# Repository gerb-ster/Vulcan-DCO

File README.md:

# Vulcan DCO

## Status: (Almost) finished*

- done: draw first schematic
- done: breadboard and test
- done: board design
- done: design frontpanel
- done: order PCB and build prototype

*) I only need to finish building a proper faceplate; otherwise this project is done.

## Theory

This DCO module is based on an article written by Alethea Flowers about the Roland Juno series. 
The idea behind this specific DCO is that a (analog) ramp generator is being controlled by 
a (digital) microcontroller. A clock signal comming from the micro controller will control the 
frequency of the ramp generator. The nature of this perticular circuit is such, that an increase of 
the frequency means an decrease of the output amplitude of the generated waveform. To counter 
this effect, a DAC is used to compensate the input voltage. If you want more in-depth information
about this, I would highly recommend you read the above mentioned article. A link is provided below.

## Requirements

For this module I aimed at the following specs

- 1v/oct control voltage (-3v to +5v)
- 8 octave range (A0 to A8)
- Triangle, Saw, Sine, Pulse, Square and Sub-Square outputs
- 1k output impedance
- 10 Vpp around 0 volts output
- PWM control for the Pulse output

## Internals

Since this systems requires a micro controller to control it, I've choosen the ATTiny84 running at 20Mhz
from Microchip for this purpose. It has all peripherals (ADC, timers, SPI) on board and it has a relative
small footprint. For the DAC I've choosen a MCP4921 which is connected to the ATTiny through SPI. To generate
a stabel reference voltage, a TL431 shunt voltage regulator is used. For all other tasks, scaling and shifting
the CV and wave generators, TL082/TL084 op-amps are used.

## General Workings

The control voltage comming in is scaled down by 2 and shifted down to 0v to translate the -3v/+5v into 0v/+4v.
Diode clamps are used to make sure the signal doesn't go below 0v or +5v. This signal is then fed to the 10bit 
ADC of the microchip, which has a AREF of 4v, so 0v has a value of 0, while 4v will have a value of 1024. This 
value is then used to determine the input voltage of the ramp genator using the DAC and the clock signal which 
controls it's frequency. The generated ramp wave is then used to generate the sine, triangle, and pulse waves
using several wave shapers. The square and sub square waves are taken directly from the clock signal comming 
from the microchip.

A simple block diagram outlining the inner workings

## The Microchip

The most interresting part of this system is the microchip controlling the ramp generator. All other parts are
more or less standard building blocks which you will find in various other VCO schematics. As mentioned above,
the microchip uses it's ADC to convert the incoming control voltage to a 10bit value which is used to control
the ramp generator. To do this, every one of these 1024 values needs to be translated to a certain clock 
frequency and an input voltage. Since this is not a linear scale, some math has to be done. I've tried to break
it down in the following sections:

### CV to Frequencies

I've used this table to translate the control voltages to frequencies. I've also added the CV value after shifting
and scaling and the correspondending ADC values. 

| CV | Norm. CV | Note | Hz | ADC Value  |
|---|---|---|---|---|
| -3v | 0.0v | A0 | 27.5 Hz | 0
| -2v | 0.5v | A1 |   55 Hz | 127
| -1v | 1.0v | A2 |  110 Hz | 255
| 0v | 1.5v | A3 |  220 Hz | 383
| 1v | 2.0v | A4 |  440 Hz | 511
| 2v | 2.5v | A5 |  880 Hz | 639
| 3v | 3.0v | A6 | 1760 Hz | 767
| 4v | 3.5v | A7 | 3520 Hz | 895
| 5v | 4.0v | A8 | 7040 Hz | 1023

The formula used here is:

```
frequency = (2 ^ (2 * normalized_control_voltage)) * 27.5
```

### Setting the Clock Frequency

For the clock signal I've used one of the Timers (timer1) of the ATTiny84. It is set up in such a
way that it generates a square wave at pin 7 with a frequency set by manipulating a compare mode
value. If you want more specifics and want to know what registers are set, please check out the 
source code, comments are provided. For every duty cycle of the squeare wave we need 2 pulses, one
to turn the output high, one to turn it low. This formula is used ('F_CPU' is the clock speed of the
CPU (20Mhz) and 'current_prescaler' is the prescaler used in this timer(8)):

```
timer_value = (F_CPU / current_prescaler) / (frequency * 2)
```

For more information about using the timer of an ATTiny84, links are provided below.

### Input Voltage Compensation

As mentioned above, we need to compensate the input voltage of the ramp generator to make sure the
amplitude of the output remains the same. To do this we use a DAC. The DAC generates a voltage between
0v and 4v, using a 12bit value (0-4096). For this we also use the 4.00v shunt voltage regulator as a
voltage reference. This voltage is then inverted and multiplied with a factor 3 to cover a range of
0v to -12v. This way the ramp generator will output a 12vpp ramp between 0v and 12v.

The formula to transform a frequency to the appropriate DAC voltage can be found in the article by
Alethea Flowers, she explains it in much better details then I can do, so if you're interested in that,
the link can be found below.

```
C = 1nF
R = 200k Ohm
Vout = +12v

time = 1 / frequency
Vin = -(C * R * Vout) / time
```

#### However... 

After a lot of testing and doing measurements I found out that this formula works, but it kind of 
starts failing for the lower frequencies. Below 300Hz you will need a higher input voltage to get a consistent
output voltage. To make it easier for myself I've picked an 10Vpp instead of 12Vpp for my measurements. I've
plotted these numbers on a graph and it turned out pretty linear so when i used the formula which came out
this graph, the low end output voltage are much more consistent.

I'm not a mathematician so why or how this formula works, i don't know :-)

```
Vin = (0.697151065 * frequency) + 40.82
```

### Lookup Tables

If you look through the source code you won't find any of the above decribed formulas. This is because 
I've used 2 lookup tables to speed things up. Although the ATTiny84 could do the Math involved, this is 
not really necessary. Every one of the 1024 values coming from ADC will translate into a 'fixed' timer and 
DAC value. So there is no real need to calculate these values on the fly. These lookup tables are basically 
2 giant arrays, 1024 elements in size, which contain all pre-calculated values. These arrays are stored in
the Flash memory of the ATTiny since the normal RAM is to small. 

In the 'utils' folder you can find the ```generator.php``` file which is used to generate those tables and 
code. I've choosen to use PHP for this, because this is my 'native' language :-).

## Waveshapers

The Square and Sub-Square outputs are derived directly from the Clock signal using various op-amps and a 
CD4013 Dual Flip-Flop IC. This schematic is taken from a design for the 'making music with a 566' by
Thomas Henry. Next, the Saw Wave coming out of the Ramp generator is used to shape it into a Triangle wave.
This Triangle wave is then used to generate a Sine wave. The Saw wave is also used to create a Pulse wave.
There is a CV input and pot to control the Pulse Width Modulation. For these wave shapers I've used 
designs from Thomas Henry, Ray Wilson and Yves Usson (YUSynth). Links are found below.

## Calibration

There are 2 trimmerpots that need to be set, in order to calibrate the Ramp Generator Core. 

CV_OFFSET => -1.5v  
VREF_SET => 4.00v  

## Links

<https://blog.thea.codes/the-design-of-the-juno-dco/>  
<https://www.geogebra.org/graphing/mfdyqrfj>  
<https://www.bristolwatch.com/ccs/TL431A.htm>  
<https://github.com/JChristensen/tinySPI>  
<https://github.com/MetreIdeas/ATtinyx4A_ADC_Example>  
<https://eleccelerator.com/avr-timer-calculator/>  
<https://maxembedded.wordpress.com/2011/06/28/avr-timers-timer1/>  
<https://www.nongnu.org/avr-libc/user-manual/pgmspace.html>  
<https://www.arduino.cc/reference/tr/language/variables/utilities/progmem/>  
<https://www.birthofasynth.com/Thomas_Henry/Pages/VCO-1.html>  
<https://yusynth.net/Modular/EN/VCO/index.html>

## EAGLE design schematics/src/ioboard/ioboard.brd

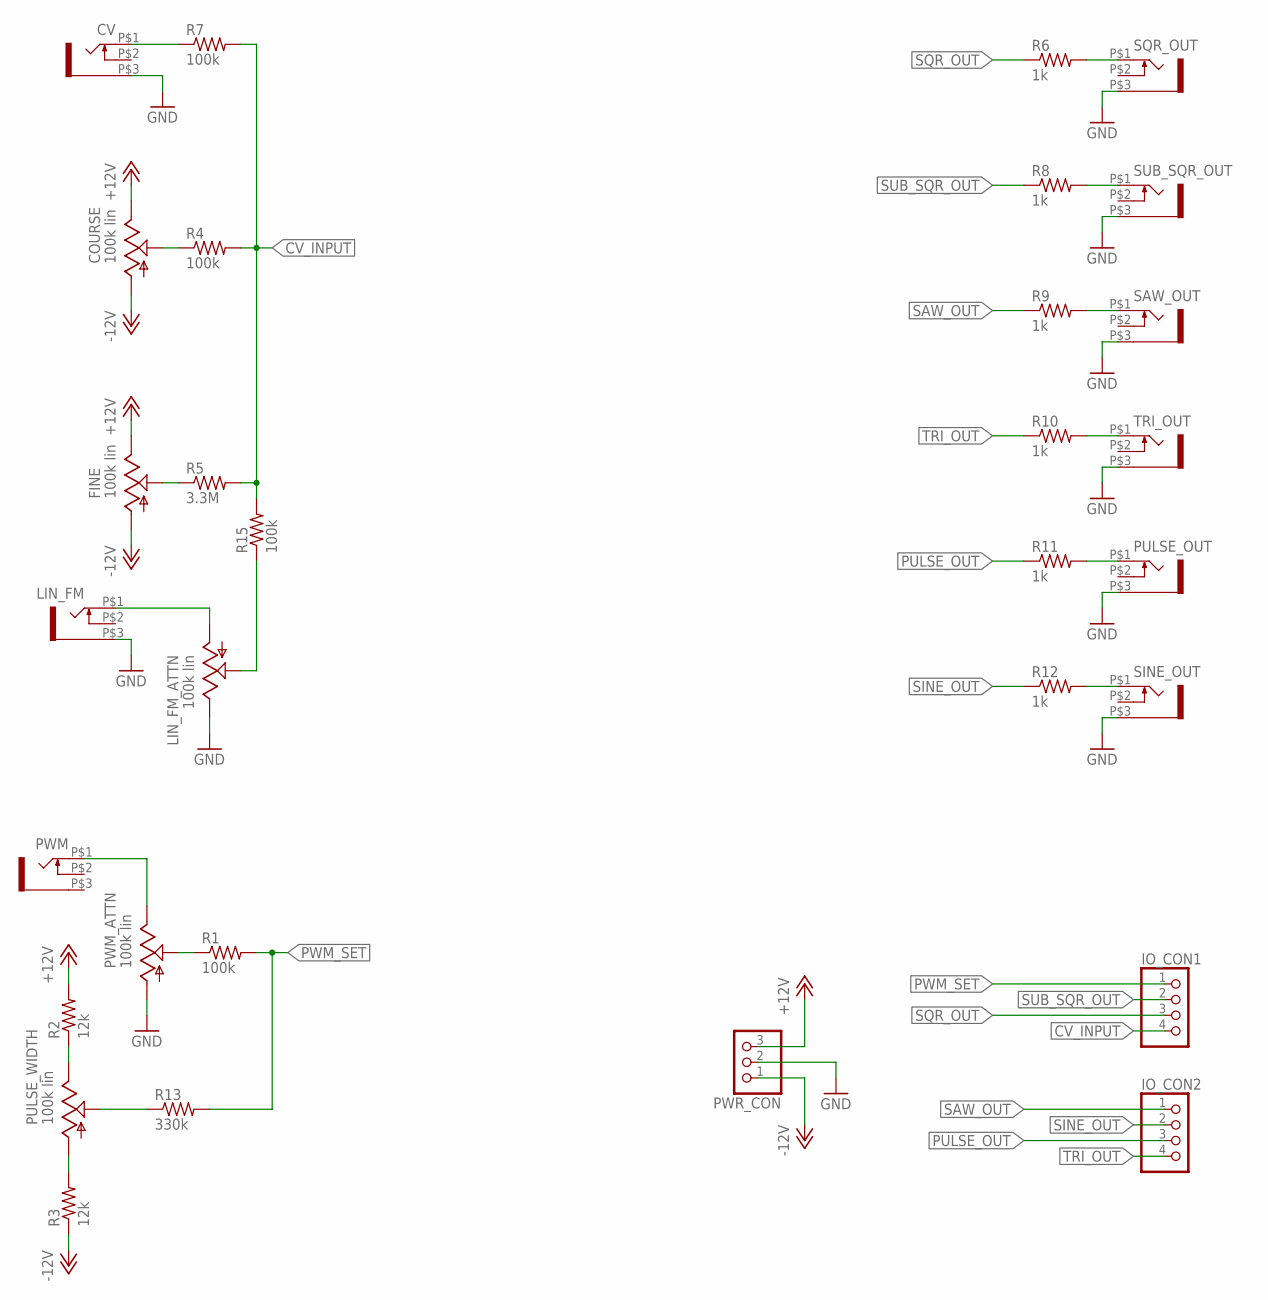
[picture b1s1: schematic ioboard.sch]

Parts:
COURSE: 100k lin; EVUF
CV: WQP-PJ301M-12_JACK
FINE: 100k lin; EVUF
IO_CON1, IO_CON2: PINHD-1X4; 1X04
LIN_FM: WQP-PJ301M-12_JACK
LIN_FM_ATTN: 100k lin; EVUF
PULSE_OUT: WQP-PJ301M-12_JACK
PULSE_WIDTH: 100k lin; EVUF
PWM: WQP-PJ301M-12_JACK
PWM_ATTN: 100k lin; EVUF
PWR_CON: PINHD-1X3; 1X03
R1, R4, R7, R15: 100k; 0207/7
R2, R3: 12k; 0207/7
R5: 3.3M; 0207/7
R6, R8, R9, R10, R11, R12: 1k; 0207/7
R13: 330k; 0207/7
SAW_OUT: WQP-PJ301M-12_JACK
SINE_OUT: WQP-PJ301M-12_JACK
SQR_OUT: WQP-PJ301M-12_JACK
SUB_SQR_OUT: WQP-PJ301M-12_JACK
TRI_OUT: WQP-PJ301M-12_JACK

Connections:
+12V: COURSE.3 (E), FINE.3 (E), PWR_CON.3, R2.2
-12V: COURSE.1 (A), FINE.1 (A), PWR_CON.1, R3.1
CV_INPUT: IO_CON1.4, R4.2, R5.2, R7.2, R15.2
GND: CV.P$3 (1), LIN_FM.P$3 (1), LIN_FM_ATTN.3 (E), PULSE_OUT.P$3 (1), PWM_ATTN.1 (A), PWR_CON.2, SAW_OUT.P$3 (1), SINE_OUT.P$3 (1), SQR_OUT.P$3 (1), SUB_SQR_OUT.P$3 (1), TRI_OUT.P$3 (1)
unnamed: COURSE.2 (S), R4.1
unnamed: FINE.2 (S), R5.1
unnamed: PULSE_WIDTH.3 (E), R2.1
unnamed: CV.P$1 (2), R7.1
unnamed: R6.2, SQR_OUT.P$1 (2)
unnamed: R8.2, SUB_SQR_OUT.P$1 (2)
unnamed: R9.2, SAW_OUT.P$1 (2)
unnamed: R10.2, TRI_OUT.P$1 (2)
unnamed: PULSE_WIDTH.1 (A), R3.2
unnamed: R12.2, SINE_OUT.P$1 (2)
unnamed: PULSE_WIDTH.2 (S), R13.1
unnamed: PWM.P$1 (2), PWM_ATTN.3 (E)
unnamed: PULSE_OUT.P$1 (2), R11.2
unnamed: PWM_ATTN.2 (S), R1.1
unnamed: LIN_FM.P$1 (2), LIN_FM_ATTN.1 (A)
unnamed: LIN_FM_ATTN.2 (S), R15.1
PULSE_OUT: IO_CON2.3, R11.1
PWM_SET: IO_CON1.1, R1.2, R13.2
SAW_OUT: IO_CON2.1, R9.1
SINE_OUT: IO_CON2.2, R12.1
SQR_OUT: IO_CON1.3, R6.1
SUB_SQR_OUT: IO_CON1.2, R8.1
TRI_OUT: IO_CON2.4, R10.1

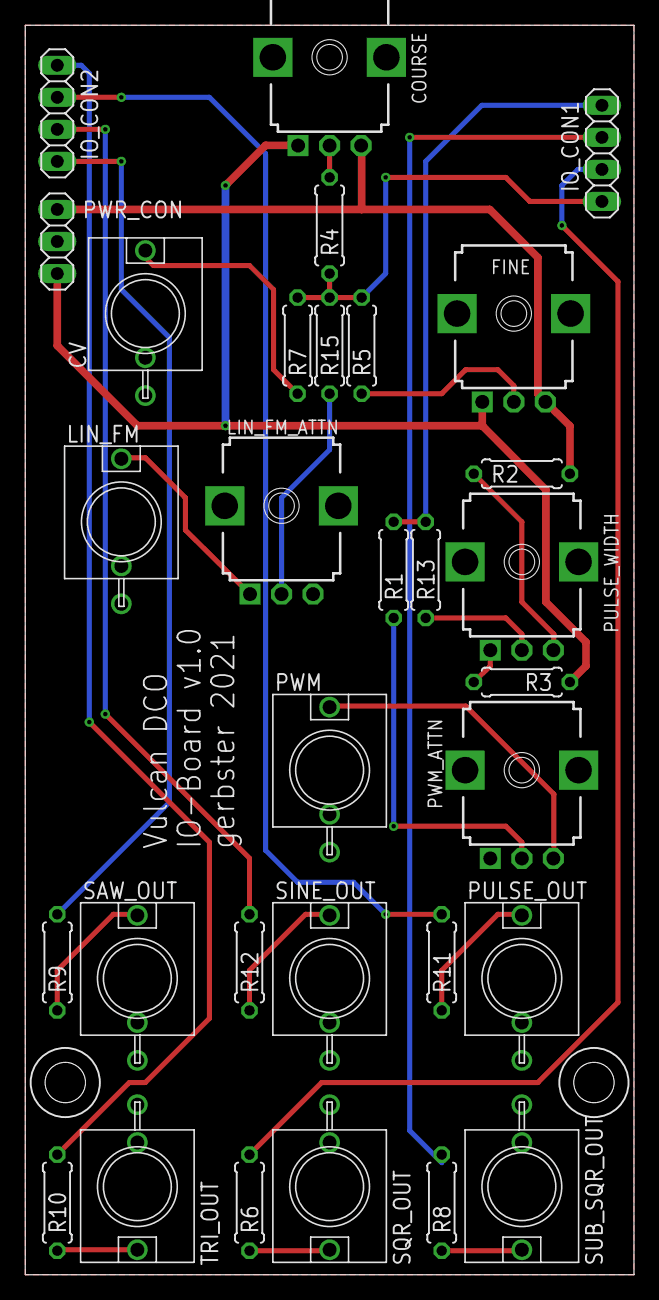
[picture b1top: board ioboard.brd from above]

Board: 2 copper layers, 48.3 x 99.1 mm, 31 parts (0 on the bottom side), 27 nets.

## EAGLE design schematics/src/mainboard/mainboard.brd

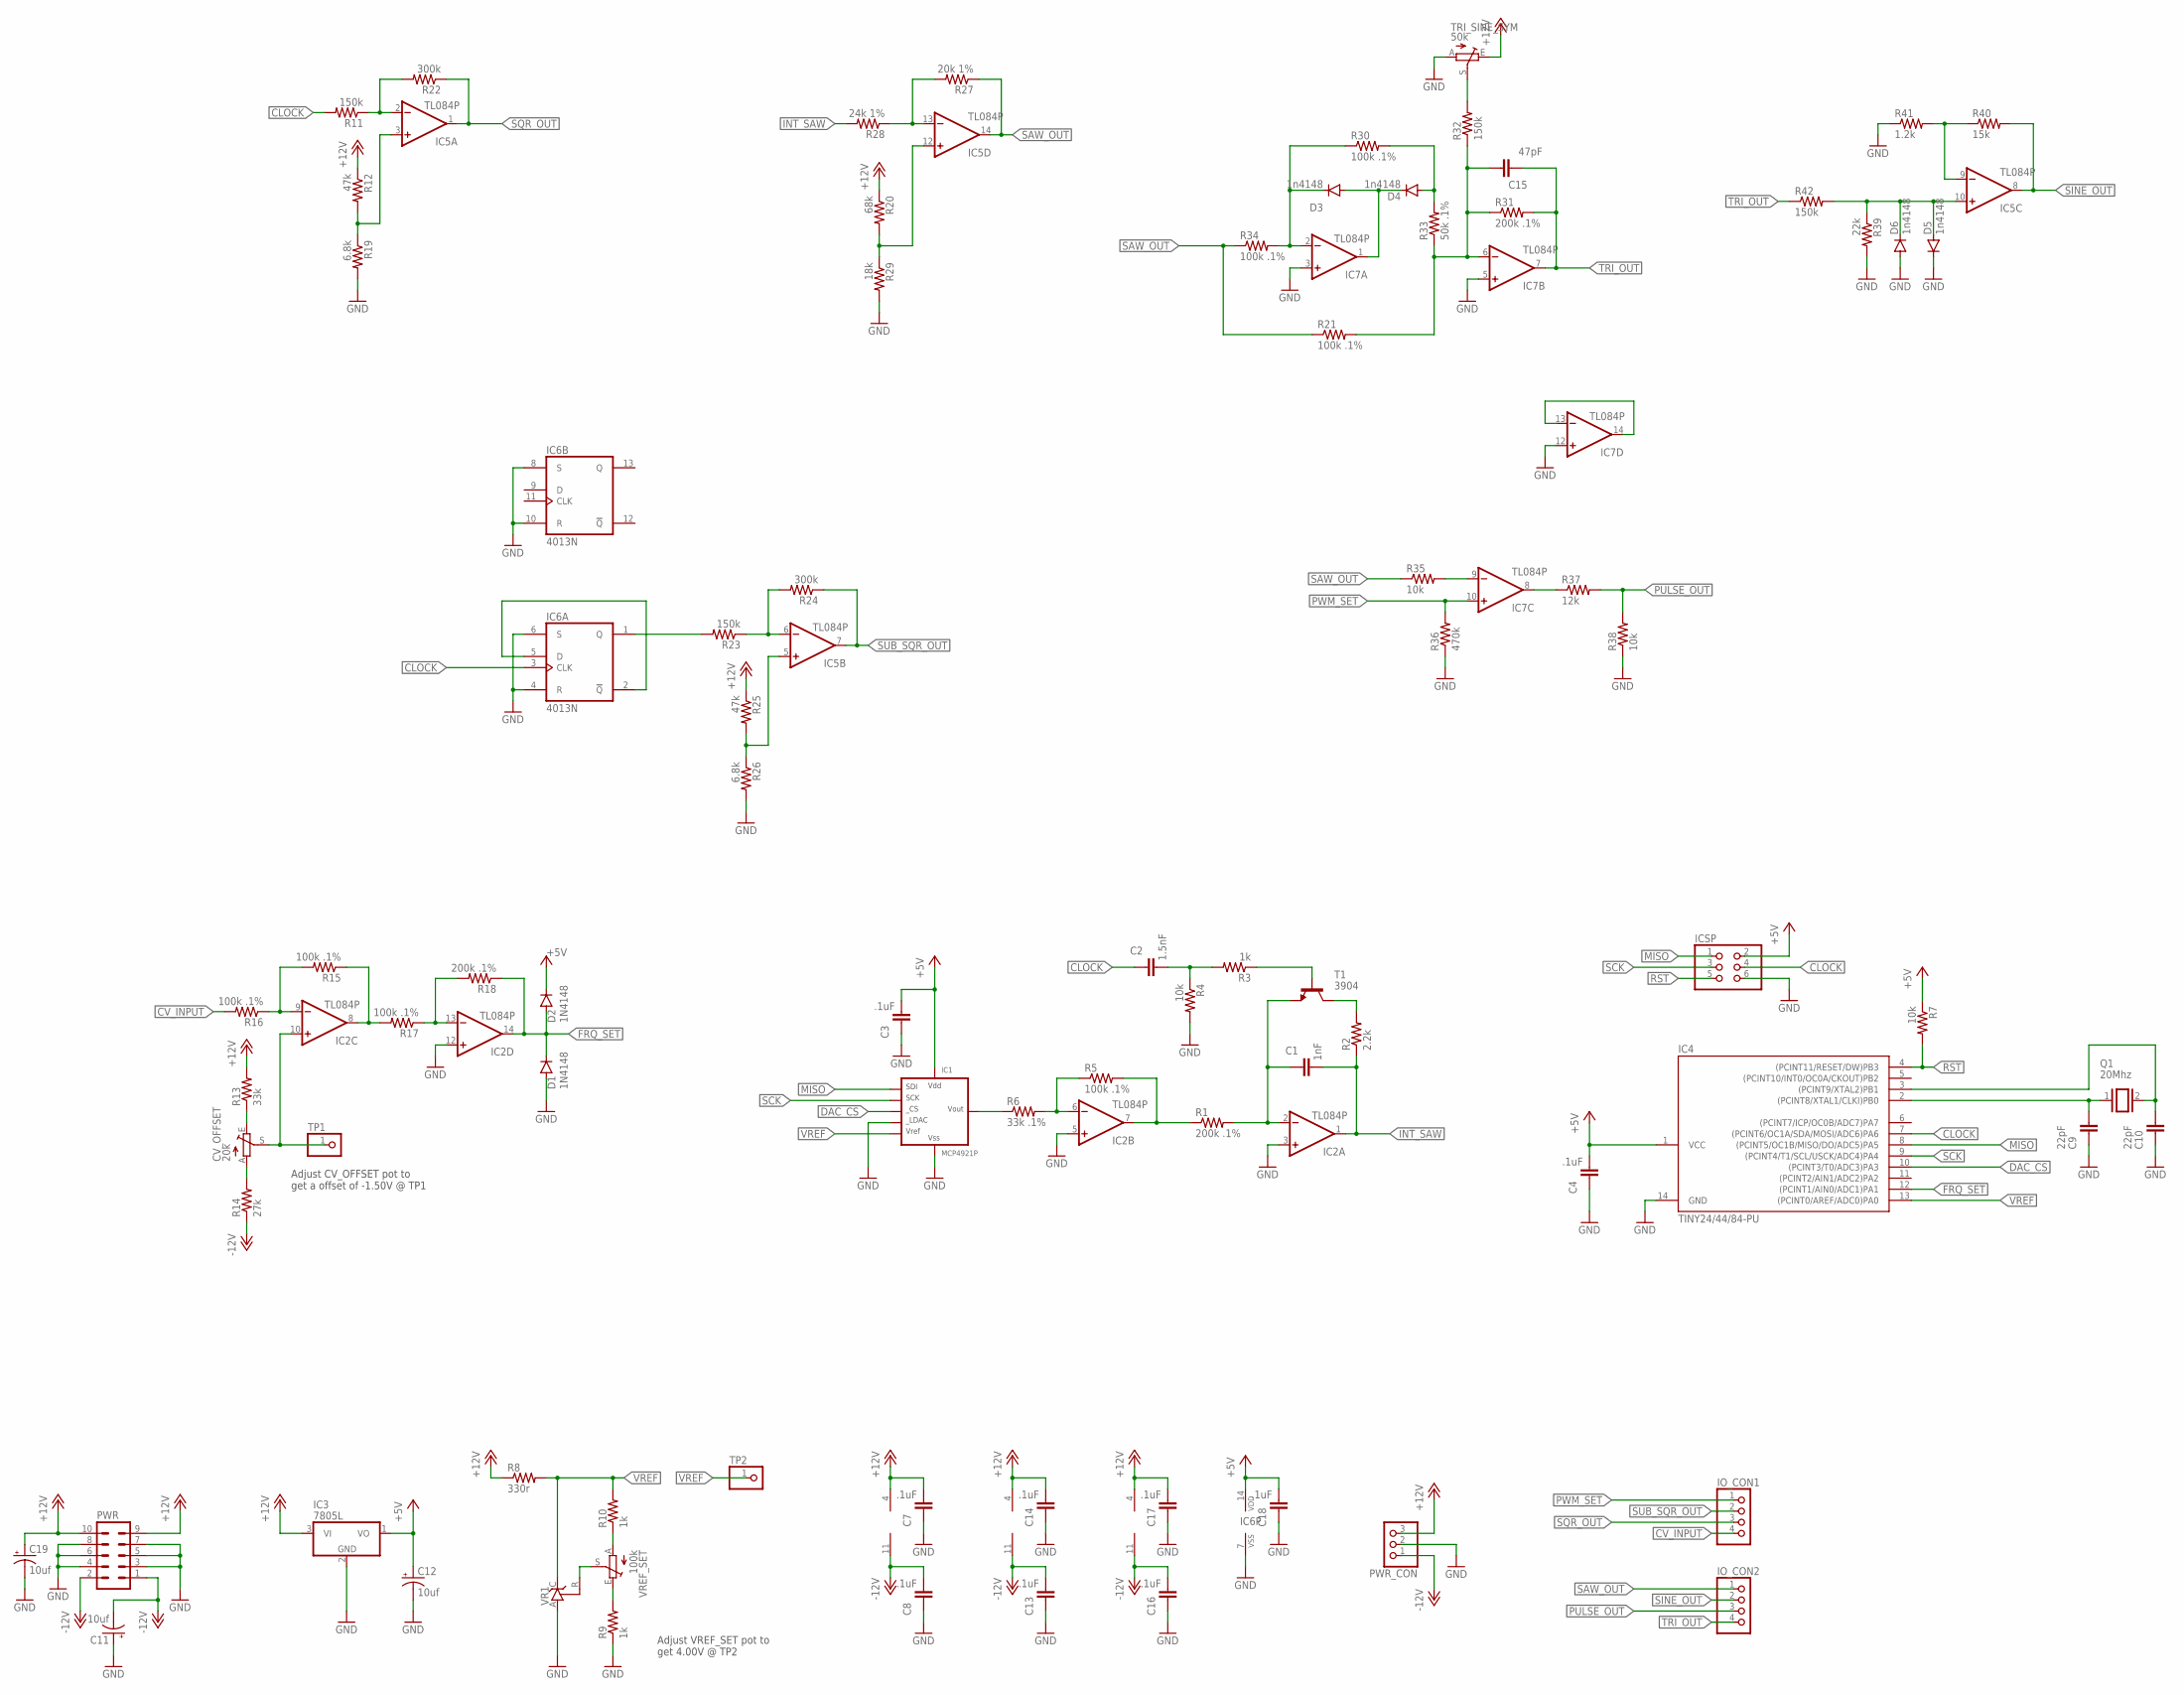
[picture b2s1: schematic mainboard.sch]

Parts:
C1: 1nF; C050-025X075
C2: 1.5nF; C050-024X044
C3, C4, C7, C8, C13, C14, C16, C17, C18: .1uF; C050-024X044
C9, C10: 22pF; C050-024X044
C11, C12, C19: 10uf; E2,5-5
C15: 47pF; C050-024X044
CV_OFFSET: 20k; S64YW
D1, D2: 1N4148; DO35-7
D3, D4, D5, D6: 1n4148; DO35-7
IC1: MCP4921P; DIL8
IC2, IC5, IC7: TL084P; DIL14
IC3: 7805L; TO92
IC4: TINY24/44/84-PU; DIL14
IC6: 4013N; DIL14
ICSP: PINHD-2X3; 2X03
IO_CON1, IO_CON2: PINHD-1X4; 1X04
PWR: ML10
PWR_CON: PINHD-1X3; 1X03
Q1: 20Mhz; QS
R1, R18, R31: 200k .1%; 0207/7
R2: 2.2k; 0207/7
R3, R9, R10: 1k; 0207/7
R4, R7, R35, R38: 10k; 0207/7
R5, R15, R16, R17, R21, R30, R34: 100k .1%; 0207/7
R6: 33k .1%; 0207/7
R8: 330r; 0207/7
R11, R23, R32, R42: 150k; 0207/7
R12, R25: 47k; 0207/7
R13: 33k; 0207/7
R14: 27k; 0207/7
R19, R26: 6.8k; 0207/7
R20: 68k; 0207/7
R22, R24: 300k; 0207/7
R27: 20k 1%; 0207/7
R28: 24k 1%; 0207/7
R29: 18k; 0207/7
R33: 50k .1%; 0207/7
R36: 470k; 0207/7
R37: 12k; 0207/7
R39: 22k; 0207/7
R40: 15k; 0207/7
R41: 1.2k; 0207/7
T1: 3904; TO92-EBC
TP1, TP2: PINHD-1X1; 1X01
TRI_SINE_SYM: 50k; S64YW
VR1: TL431CLP; TO92-CLP
VREF_SET: 100k; S64YW

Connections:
+5V: C3.2, C4.2, C12.+, C18.2, D2.C, IC1.1 (VDD), IC3.1 (VO), IC4.1 (VCC), IC6.14 (VDD), ICSP.2, R7.1
+12V: C7.2, C14.2, C17.2, C19.+, IC2.4 (V+), IC3.3 (VI), IC5.4 (V+), IC7.4 (V+), PWR.9, PWR.10, PWR_CON.3, R8.1, R12.1, R13.2, R20.1, R25.1, TRI_SINE_SYM.E
-12V: C8.2, C11.-, C13.2, C16.2, IC2.11 (V-), IC5.11 (V-), IC7.11 (V-), PWR.1, PWR.2, PWR_CON.1, R14.1
CLOCK: C2.1, IC4.7 ((PCINT6/OC1A/SDA/MOSI/ADC6)PA6), IC6.3 (CLK), ICSP.4, R11.2
CV_INPUT: IO_CON1.4, R16.2
DAC_CS: IC1.2 (CS), IC4.10 ((PCINT3/T0/ADC3)PA3)
FRQ_SET: D1.C, D2.A, IC2.14 (OUT), IC4.12 ((PCINT1/AIN0/ADC1)PA1), R18.1
GND: C3.1, C4.1, C7.1, C8.1, C9.1, C10.1, C11.+, C12.-, C13.1, C14.1, C16.1, C17.1, C18.1, C19.-, D1.A, D5.C, D6.A, IC1.5 (LDAC), IC1.7 (VSS), IC2.3 (+IN), IC2.5 (+IN), IC2.12 (+IN), IC3.2 (GND), IC4.14 (GND), IC6.4 (R), IC6.6 (S), IC6.7 (VSS), IC6.8 (S), IC6.10 (R), IC7.3 (+IN), IC7.5 (+IN), IC7.12 (+IN), ICSP.6, PWR.3, PWR.4, PWR.5, PWR.6, PWR.7, PWR.8, PWR_CON.2, R4.2, R9.1, R19.2, R26.2, R29.2, R36.1, R38.1, R39.2, R41.1, TRI_SINE_SYM.A, VR1.A
INT_SAW: C1.2, IC2.1 (OUT), R2.1, R28.2
MISO: IC1.4 (SDI), IC4.8 ((PCINT5/OC1B/MISO/DO/ADC5)PA5), ICSP.1
unnamed: C1.1, IC2.2 (-IN), R1.2, T1.E
unnamed: R2.2, T1.C
unnamed: R3.1, T1.B
unnamed: R9.2, VREF_SET.E
unnamed: C2.2, R3.2, R4.1
unnamed: IC2.7 (OUT), R1.1, R5.2
unnamed: C9.2, IC4.2 ((PCINT8/XTAL1/CLKI)PB0), Q1.1
unnamed: IC2.6 (-IN), R5.1, R6.2
unnamed: IC1.8 (VOUT), R6.1
unnamed: IC6.1 (Q), R23.2
unnamed: C10.2, IC4.3 ((PCINT9/XTAL2)PB1), Q1.2
unnamed: R10.1, VREF_SET.A
unnamed: VR1.R, VREF_SET.S
unnamed: CV_OFFSET.A, R14.2
unnamed: CV_OFFSET.E, R13.1
unnamed: CV_OFFSET.S, IC2.10 (+IN), TP1.1
unnamed: IC2.9 (-IN), R15.2, R16.1
unnamed: IC6.2 (!Q), IC6.5 (D)
unnamed: IC2.8 (OUT), R15.1, R17.2
unnamed: IC2.13 (-IN), R17.1, R18.2
unnamed: IC5.6 (-IN), R23.1, R24.2
unnamed: IC5.2 (-IN), R11.1, R22.2
unnamed: IC5.3 (+IN), R12.2, R19.1
unnamed: IC5.5 (+IN), R25.2, R26.1
unnamed: IC5.12 (+IN), R20.2, R29.1
unnamed: IC5.13 (-IN), R27.2, R28.1
unnamed: C15.2, IC7.6 (-IN), R21.2, R31.1, R32.1, R33.1
unnamed: D3.C, IC7.2 (-IN), R30.1, R34.2
unnamed: D3.A, D4.C, IC7.1 (OUT)
unnamed: D4.A, R30.2, R33.2
unnamed: IC7.8 (OUT), R37.1
unnamed: IC7.9 (-IN), R35.2
unnamed: D5.A, D6.C, IC5.10 (+IN), R39.1, R42.2
unnamed: R32.2, TRI_SINE_SYM.S
unnamed: IC7.13 (-IN), IC7.14 (OUT)
unnamed: IC5.9 (-IN), R40.1, R41.2
PULSE_OUT: IO_CON2.3, R37.2, R38.2
PWM_SET: IC7.10 (+IN), IO_CON1.1, R36.2
RST: IC4.4 ((PCINT11/RESET/DW)PB3), ICSP.5, R7.2
SAW_OUT: IC5.14 (OUT), IO_CON2.1, R21.1, R27.1, R34.1, R35.1
SCK: IC1.3 (SCK), IC4.9 ((PCINT4/T1/SCL/USCK/ADC4)PA4), ICSP.3
SINE_OUT: IC5.8 (OUT), IO_CON2.2, R40.2
SQR_OUT: IC5.1 (OUT), IO_CON1.3, R22.1
SUB_SQR_OUT: IC5.7 (OUT), IO_CON1.2, R24.1
TRI_OUT: C15.1, IC7.7 (OUT), IO_CON2.4, R31.2, R42.1
VREF: IC1.6 (VREF), IC4.13 ((PCINT0/AREF/ADC0)PA0), R8.2, R10.2, TP2.1, VR1.C

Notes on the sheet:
Adjust VREF_SET pot to get 4.00V @ TP2
Adjust CV_OFFSET pot to get a offset of -1.50V @ TP1

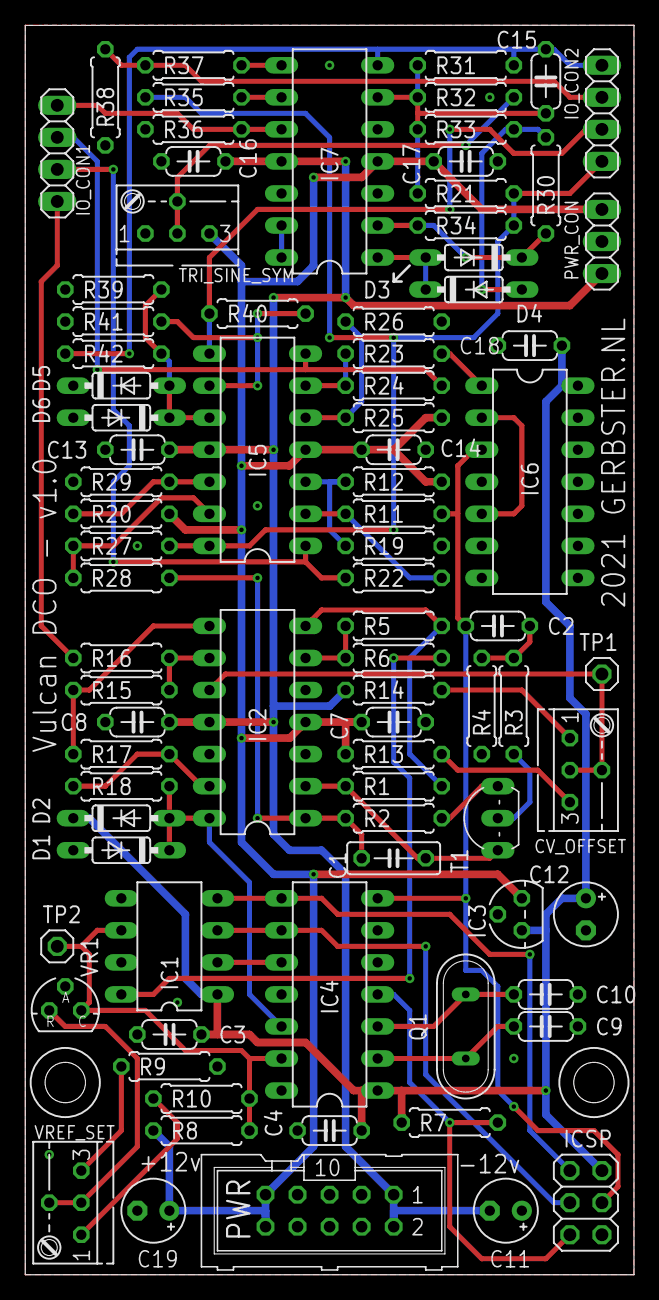
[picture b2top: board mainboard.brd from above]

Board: 2 copper layers, 48.3 x 99.1 mm, 85 parts (0 on the bottom side), 56 nets.

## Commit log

2021-05-21 add firmware files
2021-06-07 Updated Schematics & Firmware
2021-06-07 added schematic PDF's
2021-06-15 Updated Schematics, Fixed Power Socket orientation
2021-07-19 Fixed minor issues, added documentation and updated some faceplates
2021-07-19 Updated status
2021-08-06 Updated some schematics and docs
2021-08-10 Fixed some bugs and updated documentation
2021-09-26 cleanup
2021-09-26 re added files
2022-04-20 Some updates & bugfixes
2022-04-22 Fixed schematics & descriptions
2022-05-17 Updated Firmware
2022-05-18 Updated Faceplates
2022-05-18 Fixed issues
2022-05-21 Fixed schematics
2022-05-28 General updates
2022-06-13 Faceplates & Bugfixes
2023-01-06 added firmware hex files
